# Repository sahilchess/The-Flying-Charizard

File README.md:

# The Flying Charizard 

A Simple STM32-based flight controller PCB with Charizard-themed artwork etched into the board layers.

## Overview

The Flying Charizard is a fully custom PCB designed around the **STM32F722RETx** microcontroller for flight control applications.  
It combines practical avionics hardware with Pokémon-inspired PCB art across copper and silkscreen layers.

## Features

- STM32 microcontroller (**STM32F722RETx**)
- USB-C power and communication
- Battery charge management (**RA9357RNER**)
- Buck-boost converter (**TPS63070RNNR**) for stable power delivery
- Barometric pressure sensor (**BMP390**)
- Accelerometer / gyroscope (**KN-45696**) for IMU
- Dual crystal oscillators
- SD card interface
- 2x servo headers
- Reset and boot buttons
- LiPo battery connector (BAT+)
- Custom Charizard copper art across F.Cu and B.Cu layers

## Schematic Sections

| Block | Component |
|---|---|
| MCU | STM32F722RETx |
| USB-C | TYPE-C 16PIN 2MD |
| Pressure Sensor | BMP390 |
| IMU | KN-45696 (Accel/Gyro) |
| Battery Charger | RA9357RNER |
| Buck-Boost | TPS63070RNNR |
| Power Switch | LM951130 |
| SD Card | OLA-Z2869250 |

## PCB

Designed in **KiCad** as a **2-layer board** with Charizard artwork embedded in copper pours and silkscreen.

The artwork includes:
- Charizard
- Dragonite
- Charmander
- Mega Charizard X

## Gallery

### Schematic

### PCB / Artwork

## Author

[@Sahild](https://github.com/Sahild)

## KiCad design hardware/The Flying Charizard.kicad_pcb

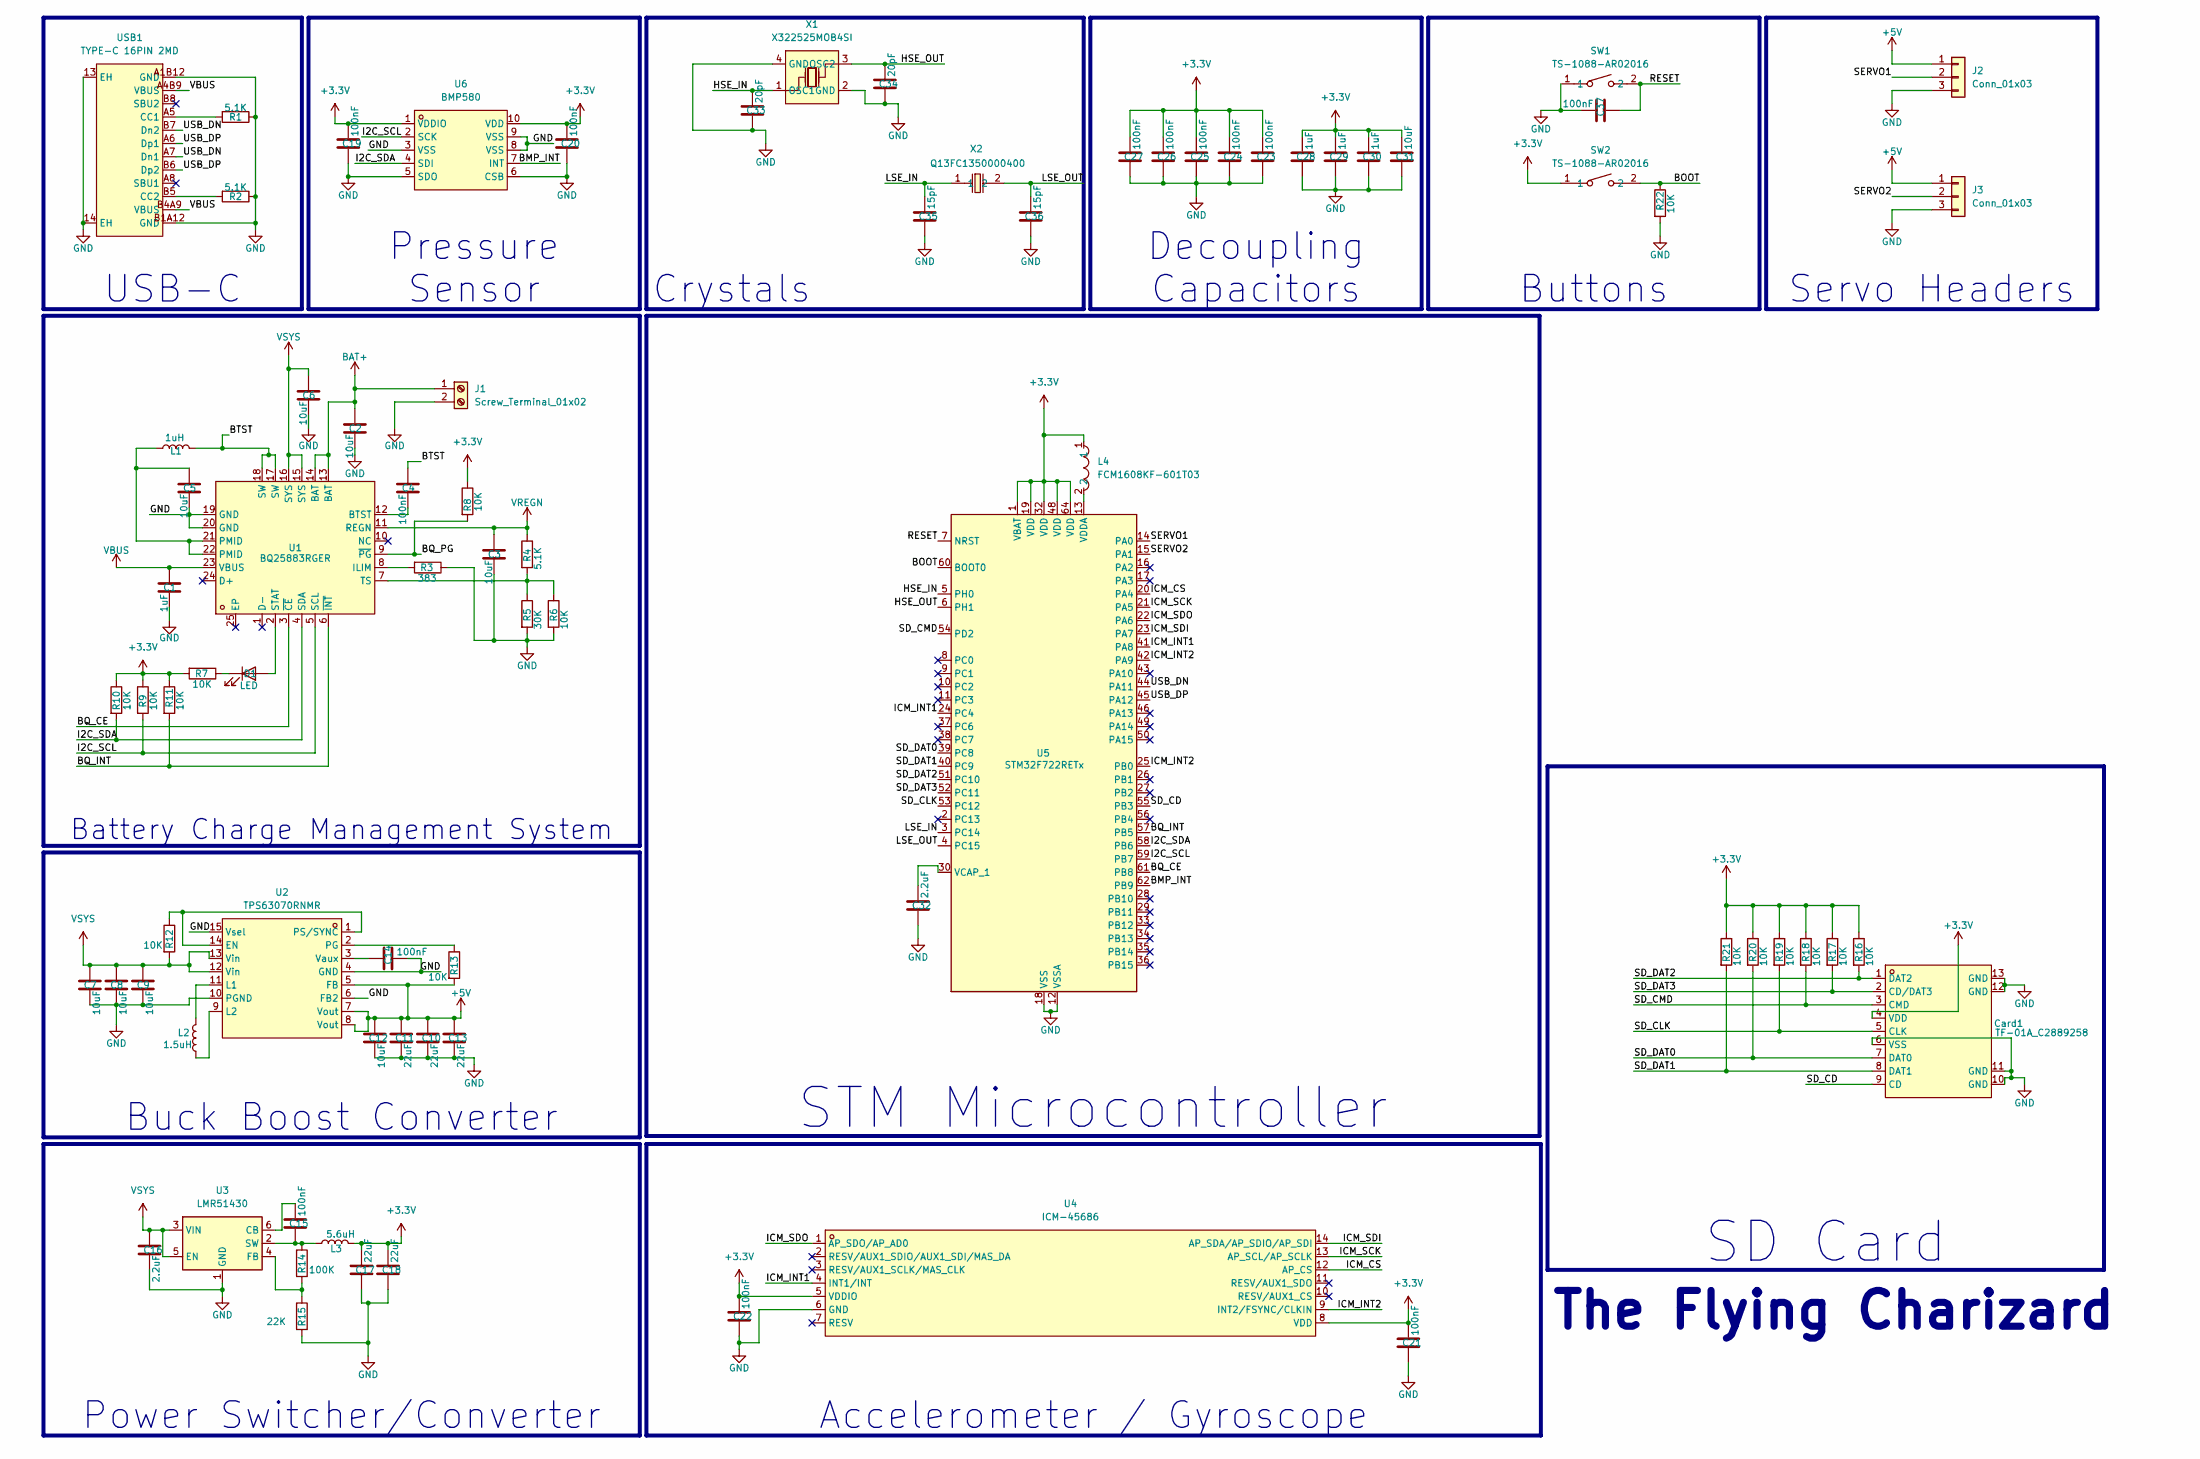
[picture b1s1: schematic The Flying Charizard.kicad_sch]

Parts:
C1, C28, C29, C30: 1uF; R_0402_1005Metric
C2, C3, C5, C6, C7, C8, C9, C12, C31: 10uF; R_0402_1005Metric
C4, C14, C15, C19, C20, C21, C22, C23, C24, C25, C26, C27, C37: 100nF; R_0402_1005Metric
C10, C11, C13, C17, C18: 22uF; R_0603_1608Metric
C16, C32: 2.2uF; R_0402_1005Metric
C33, C34: 20pF; R_0402_1005Metric
C35, C36: 15pF; R_0402_1005Metric
Card1: TF-01A_C2889258; TF-SMD_TF-02; MPN TF-01A; LCSC Part C2889258
D1: LED; LED_0603_1608Metric
J1: Screw_Terminal_01x02; TerminalBlock_Phoenix_MKDS-1,5-2_1x02_P5.00mm_Horizontal
J2, J3: Conn_01x03; PinHeader_1x03_P2.54mm_Vertical
L1: 1uH; L2520
L2: 1.5uH; IND-SMD_L4.0-W4.0-A
L3: 5.6uH; IND-SMD_L3.0-W3.0
L4: FCM1608KF-601T03; L0603; MPN FCM1608KF-601T03; LCSC Part C141723
R1, R2, R4: 5.1K; R_0402_1005Metric
R3: 383; R_0402_1005Metric
R5: 30K; R_0402_1005Metric
R6, R7, R8, R9, R10, R11, R12, R13, R16, R17, R18, R19, R20, R21, R22: 10K; R_0402_1005Metric
R14: 100K; R_0603_1608Metric
R15: 22K; R_0402_1005Metric
SW1, SW2: TS-1088-AR02016; SW-SMD_L3.9-W3.0-P4.45; MPN TS-1088-AR02016; LCSC Part C720477
U1: BQ25883RGER; VFQFPN-24_L4.0-W4.0-P0.50-BL-EP2.8; MPN BQ25883RGER; LCSC Part C544362
U2: TPS63070RNMR; VQFN-15_L3.0-W2.5-P0.50-BL; MPN TPS63070RNMR; LCSC Part C109322
U3: LMR51430; SOT-23-6_L2.9-W1.6-P0.95-LS2.8-BR
U4: ICM-45686; LGA-14_L3.0-W2.5-P0.50-TL; MPN ICM-45686; LCSC Part C22459454
U5: STM32F722RETx; LQFP-64_L10.0-W10.0-P0.50-LS12.0-BL
U6: BMP580; LGA-10_L2.0-W2.0-P0.50-TL_BMP580; MPN BMP580; LCSC Part C22391138
USB1: TYPE-C 16PIN 2MD; USB-C-SMD_TYPE-C-16PIN-2MD-073; MPN TYPE-C 16PIN 2MD(073); LCSC Part C2765186
X1: X322525MOB4SI; CRYSTAL-SMD_4P-L3.2-W2.5-BL; MPN X322525MOB4SI; LCSC Part C9006
X2: Q13FC1350000400; FC-135R_L3.2-W1.5; MPN Q13FC13500004; LCSC Part C32346

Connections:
+3.3V: C17.1, C18.1, C19.1, C20.1, C21.1, C22.1, C23.1, C24.1, C25.1, C26.1, C27.1, C28.1, C29.1, C30.1, C31.1, Card1.4 (VDD), L3.2, L4.1, R7.2, R8.1, R9.1, R10.1, R11.1, R16.1, R17.1, R18.1, R19.1, R20.1, R21.1, SW2.1, U4.5 (VDDIO), U4.8 (VDD), U5.1 (VBAT), U5.19 (VDD), U5.32 (VDD), U5.48 (VDD), U5.64 (VDD), U6.1 (VDDIO), U6.10 (VDD)
+5V: C10.1, C11.1, C12.1, C13.1, J2.1, J3.1, R13.2, U2.5 (FB), U2.7 (Vout), U2.8 (Vout)
/BMP_INT: U5.62 (PB9), U6.7 (INT)
/BOOT: R22.1, SW2.2, U5.60 (BOOT0)
/BQ_CE: U1.3 (~CE), U5.61 (PB8)
/BQ_INT: R11.2, U1.6 (~INT), U5.57 (PB5)
/BQ_PG: R8.2, U1.9 (~PG)
/BTST: C4.1, L1.2, U1.17 (SW), U1.18 (SW)
/HSE_IN: C33.1, U5.5 (PH0), X1.1 (OSC1)
/HSE_OUT: C34.1, U5.6 (PH1), X1.3 (OSC2)
/I2C_SCL: R9.2, U1.5 (SCL), U5.59 (PB7), U6.2 (SCK)
/I2C_SDA: R10.2, U1.4 (SDA), U5.58 (PB6), U6.4 (SDI)
/ICM_CS: U4.12 (AP_CS), U5.20 (PA4)
/ICM_INT1: U4.4 (INT1/INT), U5.24 (PC4), U5.41 (PA8)
/ICM_INT2: U4.9 (INT2/FSYNC/CLKIN), U5.25 (PB0), U5.42 (PA9)
/ICM_SCK: U4.13 (AP_SCL/AP_SCLK), U5.21 (PA5)
/ICM_SDI: U4.14 (AP_SDA/AP_SDIO/AP_SDI), U5.23 (PA7)
/ICM_SDO: U4.1 (AP_SDO/AP_AD0), U5.22 (PA6)
/LSE_IN: C35.1, U5.3 (PC14), X2.1
/LSE_OUT: C36.1, U5.4 (PC15), X2.2
/RESET: C37.2, SW1.2, U5.7 (NRST)
/SD_CD: Card1.9 (CD), U5.55 (PB3)
/SD_CLK: Card1.5 (CLK), R19.2, U5.53 (PC12)
/SD_CMD: Card1.3 (CMD), R18.2, U5.54 (PD2)
/SD_DAT0: Card1.7 (DAT0), R20.2, U5.39 (PC8)
/SD_DAT1: Card1.8 (DAT1), R21.2, U5.40 (PC9)
/SD_DAT2: Card1.1 (DAT2), R16.2, U5.51 (PC10)
/SD_DAT3: Card1.2 (CD/DAT3), R17.2, U5.52 (PC11)
/SERVO1: J2.2, U5.14 (PA0)
/SERVO2: J3.2, U5.15 (PA1)
/USB_DN: U5.44 (PA11), USB1.A7 (Dn1), USB1.B7 (Dn2)
/USB_DP: U5.45 (PA12), USB1.A6 (Dp1), USB1.B6 (Dp2)
BAT+: C2.1, J1.1, U1.13 (BAT), U1.14 (BAT)
GND: C1.2, C2.2, C3.2, C5.2, C6.2, C7.2, C8.2, C9.2, C10.2, C11.2, C12.2, C13.2, C14.2, C16.2, C17.2, C18.2, C19.2, C20.2, C21.2, C22.2, C23.2, C24.2, C25.2, C26.2, C27.2, C28.2, C29.2, C30.2, C31.2, C32.2, C33.2, C34.2, C35.2, C36.2, C37.1, Card1.6 (VSS), Card1.10 (GND), Card1.11 (GND), Card1.12 (GND), Card1.13 (GND), J1.2, J2.3, J3.3, R1.1, R2.1, R3.1, R5.2, R6.2, R15.2, R22.2, SW1.1, U1.19 (GND), U1.20 (GND), U2.4 (GND), U2.6 (FB2), U2.10 (PGND), U2.15 (Vsel), U3.1 (GND), U4.6 (GND), U5.12 (VSSA), U5.18 (VSS), U5.31 (VSS), U5.47 (VSS), U5.63 (VSS), U6.3 (VSS), U6.5 (SDO), U6.6 (CSB), U6.8 (VSS), U6.9 (VSS), USB1.13 (EH), USB1.14 (EH), USB1.A1B12 (GND), USB1.B1A12 (GND), X1.2 (GND), X1.4 (GND)
unnamed: C5.1, L1.1, U1.21 (PMID), U1.22 (PMID)
unnamed: D1.2 (A), U1.2 (STAT)
unnamed: D1.1 (K), R7.1
unnamed: C4.2, U1.12 (BTST)
unnamed: R3.2, U1.8 (ILIM)
unnamed: R4.2, R5.1, R6.1, U1.7 (TS)
unnamed: R12.1, U2.1 (PS/SYNC), U2.14 (EN)
unnamed: L2.2, U2.11 (L1)
unnamed: L2.1, U2.9 (L2)
unnamed: R13.1, U2.2 (PG)
unnamed: C14.1, U2.3 (Vaux)
unnamed: C15.1, U3.6 (CB)
unnamed: R14.2, R15.1, U3.4 (FB)
unnamed: C15.2, L3.1, R14.1, U3.2 (SW)
unnamed: C32.1, U5.30 (VCAP_1)
unnamed: L4.2, U5.13 (VDDA)
unnamed: R1.2, USB1.A5 (CC1)
unnamed: R2.2, USB1.B5 (CC2)
VBUS: C1.1, U1.23 (VBUS), USB1.A4B9 (VBUS), USB1.B4A9 (VBUS)
VREGN: C3.1, R4.1, U1.11 (REGN)
VSYS: C6.1, C7.1, C8.1, C9.1, C16.1, R12.2, U1.15 (SYS), U1.16 (SYS), U2.12 (Vin), U2.13 (Vin), U3.3 (VIN), U3.5 (EN)

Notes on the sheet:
The Flying Charizard
USB-C
Servo Headers
STM Microcontroller
Crystals
Power Switcher/Converter
Buttons
Decoupling Capacitors
Battery Charge Management System
Pressure Sensor
Accelerometer / Gyroscope
Buck Boost Converter
SD Card

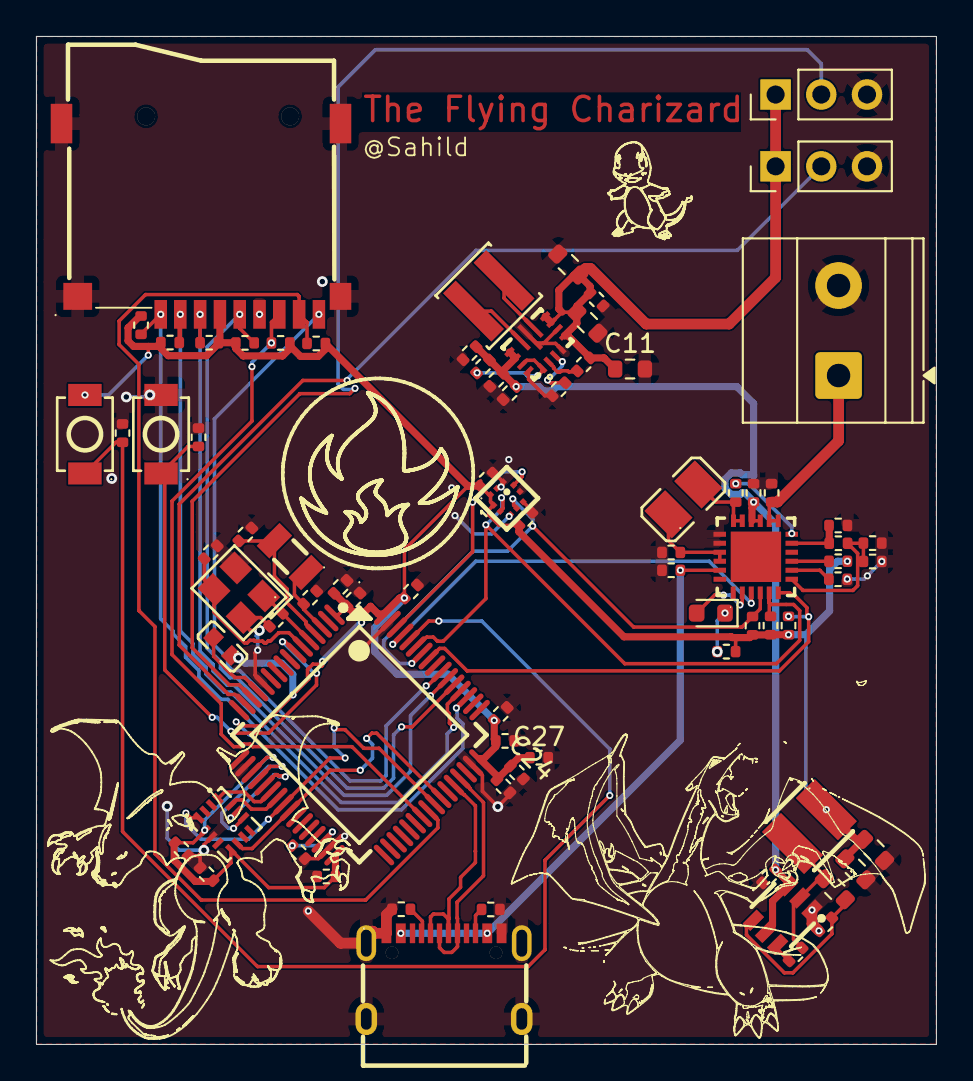
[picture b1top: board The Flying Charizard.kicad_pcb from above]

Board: 2 copper layers, 50.0 x 56.0 mm, 79 parts (0 on the bottom side), 55 nets.

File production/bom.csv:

Designator,Footprint,Quantity,Value,LCSC Part #
"C1, C28, C29, C30",0402,4,1uF,
"C10, C13, C17, C18",0603,4,22uF,
"C12, C2, C3, C31, C5, C6, C7, C8, C9",0402,9,10uF,
"C14, C15, C19, C20, C21, C22, C23, C25, C26, C37",0402,10,100nF,
"C16, C32",0402,2,2.2uF,
"C33, C34",0402,2,20pF,
"C35, C36",0402,2,6.8pF,
C4,0402,1,47nF,
CARD1,TF-SMD_TF-02,1,TF-01A_C2889258,C2889258
D1,0603,1,LED,
J1,"TerminalBlock_Phoenix_MKDS-1,5-2_1x02_P5.00mm_Horizontal",1,Screw_Terminal_01x02,
"J2, J3",PinHeader_1x03_P2.54mm_Vertical,2,Conn_01x03,
L1,L2520,1,1uH,C435392
L2,IND-SMD_L4.0-W4.0-A,1,1.5uH,C3033018
L3,IND-SMD_L3.0-W3.0,1,5.6uH,C18236327
L4,L0603,1,FCM1608KF-601T03,C141723
"R1, R2",0402,2,5.1K,
"R10, R11, R12, R13, R16, R17, R18, R19, R20, R21, R22, R6, R8, R9",0402,14,10K,
R14,0603,1,100K,
R15,0402,1,22.1K,
R3,0402,1,383,
R4,0402,1,5.23K,
R5,0402,1,30.1K,
"SW1, SW2",SW-SMD_L3.9-W3.0-P4.45,2,TS-1088-AR02016,C720477
U1,VFQFPN-24_L4.0-W4.0-P0.50-BL-EP2.8,1,BQ25883RGER,C544362
U2,VQFN-15_L3.0-W2.5-P0.50-BL,1,TPS63070RNMR,C109322
U3,SOT-23-6_L2.9-W1.6-P0.95-LS2.8-BR,1,LMR51430,C5210749
U4,LGA-14_L3.0-W2.5-P0.50-TL,1,ICM-45686,C22459454
U5,LQFP-64_L10.0-W10.0-P0.50-LS12.0-BL,1,STM32F722RETx,C118207
U6,LGA-10_L2.0-W2.0-P0.50-TL_BMP580,1,BMP580,C22391138
USB1,USB-C-SMD_TYPE-C-16PIN-2MD-073,1,TYPE-C 16PIN 2MD,C2765186
X1,CRYSTAL-SMD_4P-L3.2-W2.5-BL,1,X322525MOB4SI,C9006
X2,FC-135R_L3.2-W1.5,1,Q13FC1350000400,C32346

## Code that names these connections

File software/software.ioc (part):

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Mcu.Name=STM32F722R(C-E)Tx
Mcu.Package=LQFP64
Mcu.UserName=STM32F722RETx
PA0-WKUP.Signal=S_TIM2_CH1_ETR
PA1.Signal=S_TIM2_CH2
PA11.Mode=Host_Only
PA11.Signal=USB_OTG_FS_DM
PA12.Mode=Host_Only
PA12.Signal=USB_OTG_FS_DP
PA4.Mode=NSS_Signal_Hard_Output
PA4.Signal=SPI1_NSS
PA5.Mode=Full_Duplex_Master
PA5.Signal=SPI1_SCK
PA6.Mode=Full_Duplex_Master
PA6.Signal=SPI1_MISO
PA7.Mode=Full_Duplex_Master
PA7.Signal=SPI1_MOSI
PB0.GPIOParameters=GPIO_Label
PB0.GPIO_Label=ICM_INT2
PB0.Signal=GPXTI0
PB3.GPIOParameters=GPIO_Label
PB3.GPIO_Label=SD_CS
PB3.Signal=GPIO_Input
PB5.GPIOParameters=GPIO_Label
PB5.GPIO_Label=BQ_INT
PB5.Signal=GPXTI5
PB6.Mode=I2C
PB6.Signal=I2C1_SCL
PB7.Mode=I2C
PB7.Signal=I2C1_SDA
PB8.GPIOParameters=GPIO_Label
PB8.GPIO_Label=BQ_CE
PB8.Signal=GPIO_Output
PB9.GPIOParameters=GPIO_Label
PB9.GPIO_Label=BMP_INT
PB9.Signal=GPXTI9
PC10.Mode=SD_4_bits_Wide_bus
PC10.Signal=SDMMC1_D2
PC11.Mode=SD_4_bits_Wide_bus
PC11.Signal=SDMMC1_D3
PC12.Mode=SD_4_bits_Wide_bus
PC12.Signal=SDMMC1_CK
PC14-OSC32_IN.Mode=LSE-External-Oscillator
PC14-OSC32_IN.Signal=RCC_OSC32_IN
PC15-OSC32_OUT.Mode=LSE-External-Oscillator
PC15-OSC32_OUT.Signal=RCC_OSC32_OUT
PC8.Mode=SD_4_bits_Wide_bus
PC8.Signal=SDMMC1_D0
PC9.Mode=SD_4_bits_Wide_bus
PC9.Signal=SDMMC1_D1
PD2.Mode=SD_4_bits_Wide_bus
PD2.Signal=SDMMC1_CMD
PH0-OSC_IN.Mode=HSE-External-Oscillator
PH0-OSC_IN.Signal=RCC_OSC_IN
PH1-OSC_OUT.Mode=HSE-External-Oscillator
PH1-OSC_OUT.Signal=RCC_OSC_OUT
RCC.HSE_VALUE=25000000
board=custom

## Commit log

2026-05-30 Add project README with expanded image gallery
2026-05-30 Add README for Flying Charizard flight controller
    Added detailed description of the Flying Charizard flight controller PCB, including features, schematic sections, PCB design, and gallery.
2026-06-21 production stuff
